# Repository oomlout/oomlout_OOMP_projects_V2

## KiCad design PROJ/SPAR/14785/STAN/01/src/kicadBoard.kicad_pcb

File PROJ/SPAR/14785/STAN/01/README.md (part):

Contents
========

* [PRPR14785 > Pro RF](#prpr14785--pro-rf)
	* [OOMP Parts](#oomp-parts)
	* [Images](#images)
	* [Tags](#tags)
  
![][im]
# PRPR14785 > Pro RF

- ID: PROJ-SPAR-14785-STAN-01
- Hex ID: PRPR14785
- Name: Pro RF
- Path: oomlout_OOMP_projects_V2/PROJ/SPAR/14785/STAN/01/
- Description: Pro RF
- Long Link: [http://oom.lt/PROJ-SPAR-14785-STAN-01](http://oom.lt/PROJ-SPAR-14785-STAN-01)
- Short Link: [http://oom.lt/PRPR14785](http://oom.lt/PRPR14785)

## OOMP Parts

|Image|OOMP ID|Designators|
| :--- | :--- | :--- |
||[CAPC-0603-X-NF100-V50](https://github.com/oomlout/oomlout_OOMP_parts_V2/tree/main/CAPC/0603/X/NF100/V50/)|[C14,C11,C4](https://github.com/oomlout/oomlout_OOMP_parts_V2/tree/main/CAPC/0603/X/NF100/V50/)|
||[CAPC-0603-X-PF22-V50](https://github.com/oomlout/oomlout_OOMP_parts_V2/tree/main/CAPC/0603/X/PF22/V50/)|[C7,C5](https://github.com/oomlout/oomlout_OOMP_parts_V2/tree/main/CAPC/0603/X/PF22/V50/)|
||[CAPC-0603-X-UF1-V50](https://github.com/oomlout/oomlout_OOMP_parts_V2/tree/main/CAPC/0603/X/UF1/V50/)|[C12,C8](https://github.com/oomlout/oomlout_OOMP_parts_V2/tree/main/CAPC/0603/X/UF1/V50/)|
||[CAPC-0603-X-UF47D-V16](https://github.com/oomlout/oomlout_OOMP_parts_V2/tree/main/CAPC/0603/X/UF47D/V16/)|[C9](https://github.com/oomlout/oomlout_OOMP_parts_V2/tree/main/CAPC/0603/X/UF47D/V16/)|
||CAPT-3216-X-UF10-V10|C13,C1|
||[HEAD-I01-X-PI01-01](https://github.com/oomlout/oomlout_OOMP_parts_V2/tree/main/HEAD/I01/X/PI01/01/)|[J4](https://github.com/oomlout/oomlout_OOMP_parts_V2/tree/main/HEAD/I01/X/PI01/01/)|
||[HEAD-I01-X-PI02-01](https://github.com/oomlout/oomlout_OOMP_parts_V2/tree/main/HEAD/I01/X/PI02/01/)|[J7,J12,J9,J8](https://github.com/oomlout/oomlout_OOMP_parts_V2/tree/main/HEAD/I01/X/PI02/01/)|
||[HEAD-I01-X-PI09-01](https://github.com/oomlout/oomlout_OOMP_parts_V2/tree/main/HEAD/I01/X/PI09/01/)|[J11,J5](https://github.com/oomlout/oomlout_OOMP_parts_V2/tree/main/HEAD/I01/X/PI09/01/)|
||[HEAD-I01-X-PI10-01](https://github.com/oomlout/oomlout_OOMP_parts_V2/tree/main/HEAD/I01/X/PI10/01/)|[J6,J3](https://github.com/oomlout/oomlout_OOMP_parts_V2/tree/main/HEAD/I01/X/PI10/01/)|
||HEAD-I01-X-UNMATCHED-01|J13|
||[HEAD-JSTSH-X-PI04-RS](https://github.com/oomlout/oomlout_OOMP_parts_V2/tree/main/HEAD/JSTSH/X/PI04/RS/)|[J2](https://github.com/oomlout/oomlout_OOMP_parts_V2/tree/main/HEAD/JSTSH/X/PI04/RS/)|
||[LEDS-0603-G-STAN-01](https://github.com/oomlout/oomlout_OOMP_parts_V2/tree/main/LEDS/0603/G/STAN/01/)|[D1](https://github.com/oomlout/oomlout_OOMP_parts_V2/tree/main/LEDS/0603/G/STAN/01/)|
||[LEDS-0603-L-STAN-01](https://github.com/oomlout/oomlout_OOMP_parts_V2/tree/main/LEDS/0603/L/STAN/01/)|[D2](https://github.com/oomlout/oomlout_OOMP_parts_V2/tree/main/LEDS/0603/L/STAN/01/)|
||[LEDS-0603-R-STAN-01](https://github.com/oomlout/oomlout_OOMP_parts_V2/tree/main/LEDS/0603/R/STAN/01/)|[LED1](https://github.com/oomlout/oomlout_OOMP_parts_V2/tree/main/LEDS/0603/R/STAN/01/)|
||[LEDS-0603-Y-STAN-01](https://github.com/oomlout/oomlout_OOMP_parts_V2/tree/main/LEDS/0603/Y/STAN/01/)|[D6,D4](https://github.com/oomlout/oomlout_OOMP_parts_V2/tree/main/LEDS/0603/Y/STAN/01/)|
||[RESE-0603-X-O102-01](https://github.com/oomlout/oomlout_OOMP_parts_V2/tree/main/RESE/0603/X/O102/01/)|[R13,R9,R3,R10,R7](https://github.com/oomlout/oomlout_OOMP_parts_V2/tree/main/RESE/0603/X/O102/01/)|
||[RESE-0603-X-O103-01](https://github.com/oomlout/oomlout_OOMP_parts_V2/tree/main/RESE/0603/X/O103/01/)|[R4,R6,R1,R2](https://github.com/oomlout/oomlout_OOMP_parts_V2/tree/main/RESE/0603/X/O103/01/)|
||[RESE-0603-X-O202-01](https://github.com/oomlout/oomlout_OOMP_parts_V2/tree/main/RESE/0603/X/O202/01/)|[R5](https://github.com/oomlout/oomlout_OOMP_parts_V2/tree/main/RESE/0603/X/O202/01/)|
||[RESE-0603-X-O220-01](https://github.com/oomlout/oomlout_OOMP_parts_V2/tree/main/RESE/0603/X/O220/01/)|[R11,R12](https://github.com/oomlout/oomlout_OOMP_parts_V2/tree/main/RESE/0603/X/O220/01/)|
||UNMATCHED-1206-X-UNMATCHED-01|F1|
||UNMATCHED-SO235-X-UNMATCHED-01|U1,U6|
||UNMATCHED-UNMATCHED-X-UNMATCHED-01|U3,Y2,S3,S1,U2|
||USBS-UNMATCHED-X-UNMATCHED-01|J1|
||||

## Images

|kicadPcb3dFront<br>|kicadPcb3dBack<br>|kicadPcb3d<br>|pcbdraw<br>|
| :---: | :---: | :---: | :---: |
|pcbdrawBack<br>||||

## Tags

|Tag Name|Tag Code|Tag Value|
| :--- | :--- | :--- |
|OOMP Type|oompType|PROJ|
|OOMP Size|oompSize|SPAR|
|OOMP Color|oompColor|14785|
|OOMP Description|oompDesc|STAN|
|OOMP Index|oompIndex|01|
|Full OOMP ID|oompID|PROJ-SPAR-14785-STAN-01|
|Hex ID (short code)|hexID|PRPR14785|
|name|name|Pro RF|
|gitRepo|gitRepo|https://github.com/sparkfun/Pro_RF|
|gitName|gitName|Pro_RF|
|eagleBoard|eagleBoard|/Hardware/Pro_RF.brd|
|eagleSchem|eagleSchem|/Hardware/Pro_RF.sch|
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
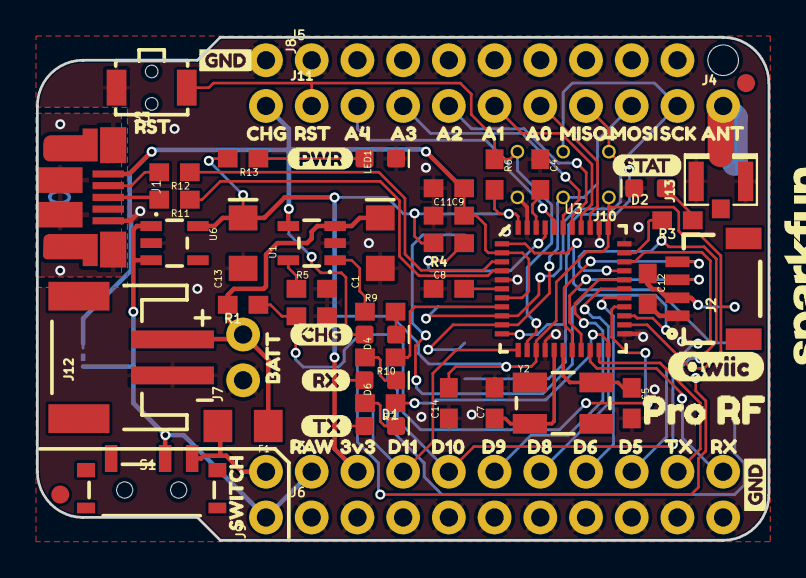
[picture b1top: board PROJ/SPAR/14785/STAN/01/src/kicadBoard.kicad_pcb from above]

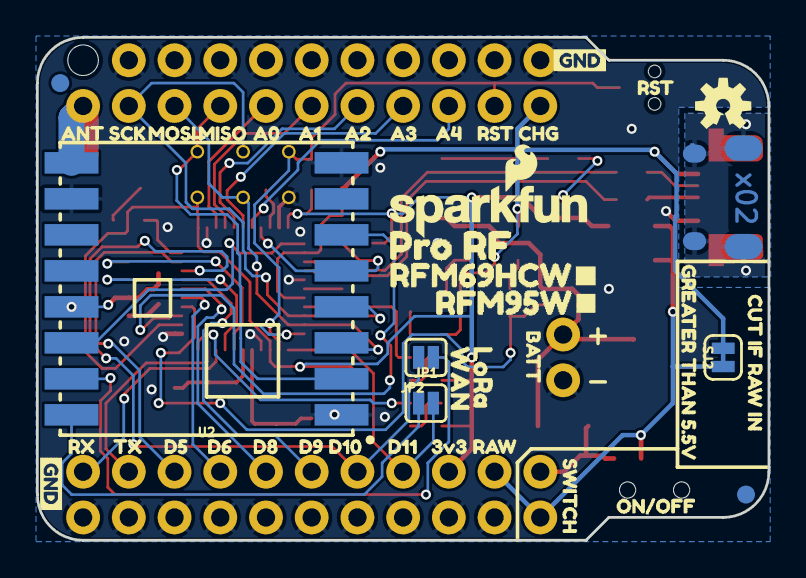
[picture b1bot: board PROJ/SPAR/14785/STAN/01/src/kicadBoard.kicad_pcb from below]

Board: 2 copper layers, 40.6 x 27.9 mm, 129 parts (42 on the bottom side), 51 nets.

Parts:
@HOLE0: (no value)
C1, C13: 10uF; EIA3216
C4, C11, C14: 0.1uF; 0603
C5, C7: 22pF; 0603
C8, C12: 1.0uF; 0603
C9: 4.7uF; 0603
D1: Green; LED-0603
D2: BLUE; LED-0603
D4, D6: Yellow; LED-0603
F1: 6V/0.5A; 1206
FD1, FD2, FD3, FD4: FIDUCIAL1X2; FIDUCIAL-1X2
FRAME2: FRAME-LEDGER; CREATIVE_COMMONS
J1: USB-MICROB-PTH-MILL
J2: 1X04_1MM_RA
J3, J6: 1X10_NO_SILK
J4: 1X01_NO_SILK
J5, J11: 1X09_NO_SILK
J7: PTH; 1X02_NO_SILK
J8: 1X02_NO_SILK
J9: External On/Off; 1X02_NO_SILK
J10: AVR_SPI_PROG_3X2TESTPOINTS; 2X3_TEST_POINTS
J12: JST; JST-2-SMD
J13: U.FL
JP1, JP2: SMT-JUMPER_2_NO_SILK
LED1: RED; LED-0603
LOGO1: REVISION
LOGO2: SFE_LOGO_NAME.1_INCH; SFE_LOGO_NAME_.1
LOGO3: SFE_LOGO_NAME_FLAME.1_INCH; SFE_LOGO_NAME_FLAME_.1
R1, R2, R4, R6: 10k; 0603
R3, R7, R9, R10, R13: 1k; 0603
R5: 2.0k; 0603
R11, R12: 22; 0603
S1: Power; SWITCH_SPST_SMD_A
S3: TACTILE_SWITCH_SMD_RIGHT_ANGLE
SJ2: USB Power; SMT-JUMPER_2_NC_TRACE_SILK
U1: MCP73831; SOT23-5
U2: 915MHz; RFM69HCW-XXXS2
U3: 32U4; QFN-44-NOPAD
U6: 3.3V; SOT23-5
U$1, U$31: PRO_RF0
U$3, U$42: A43
U$4, U$43: A34
U$5, U$44: A25
U$6, U$45: A16
U$7, U$46: A07
U$8, U$47: MISO8
U$9, U$48: MOSI9
U$10, U$49: SCK10
U$11, U$50: ANT11
U$12, U$17, U$38, U$62: GND0
U$13, U$28, U$36, U$41: RST2
U$14, U$40, U$65: CHG1
U$15, U$16: D90
U$18, U$58: D615
U$19, U$73: RX2
U$20, U$56: D817
U$21, U$68: D100
U$22, U$54: D1119
U$23, U$53: 3V320
U$24, U$52: RAW21
U$25: LORA0
U$26: SPECIAL_INSTRUCTIONS-ORDERING; ORDERING_INSTRUCTIONS
U$27, U$37: SWITCH23
U$29, U$32: BATT25
U$33: CUT_IF_RAW_IN0
U$34: GREATER_THAN_5#5V1
U$35: WAN1
U$39: ON#OFF0
U$51: OSHW-LOGO-S
U$55, U$74: D514
U$57, U$69: TX3
U$59: RFM69HCW#1
U$60: RFM95W#0
U$63: PWR-()-03
U$66: QWIIC-()-04
U$70: TX6
U$71: STAT5
U$72: RX7
Y2: 8MHz; CRYSTAL-SMD-5X3.2-4PAD

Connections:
3.3V: C12.1, C13.+, C14.2, D1.A, D6.A, J2.2, J3.2, J10.2, R4.2, R6.2, R13.2, U2.13, U3.14, U3.24, U3.34, U3.44, U6.5
A0: J11.6, U3.36
A1: J11.5, U3.37
A2: J11.4, U3.38
A3: J11.3, U3.39
A4: J11.2, U3.40
ANT: J4.1, J13.FEED, U2.9
AREF: C4.2, U3.42
CHARGE_STAT: R9.1, U1.1
D5: J3.8, U3.31
D6: J3.7, U3.27
D8: J3.6, U3.28
D9: J3.5, U3.29
D10: J3.4, JP1.2, U3.30
D11: J3.3, JP2.2, U3.12
D+: R11.1, U3.4
D-: R12.1, U3.3
GND: C1.-, C4.1, C5.2, C7.2, C8.1, C9.2, C11.1, C12.2, C13.-, C14.1, D2.C, J1.GND, J2.1, J5.1, J5.2, J5.3, J5.4, J5.5, J5.6, J5.7, J5.8, J5.9, J6.1, J6.2, J6.3, J6.4, J6.5, J6.6, J6.7, J6.8, J6.9, J6.10, J7.1, J8.1, J10.6, J12.1, J13.1, J13.2, LED1.C, R2.1, R5.2, S3.2, U1.2, U2.1, U2.8, U2.10, U3.5, U3.15, U3.23, U3.33, U3.35, U3.43, U6.2
MISO: J10.1, J11.7, U2.2, U3.11
MOSI: J10.4, J11.8, U2.3, U3.10
unnamed: D6.C, R10.2
unnamed: D1.C, R7.2
unnamed: D2.A, R3.1
unnamed: C5.1, U3.17, Y2.3
unnamed: J1.D+, R11.2
unnamed: C7.1, U3.16, Y2.1
unnamed: D4.C, R9.2
unnamed: F1.2, J9.2, S1.1
unnamed: R5.1, U1.5
unnamed: J1.D-, R12.2
unnamed: LED1.A, R13.1
RAW: J3.1, J9.1, S1.2, SJ2.1, U6.1, U6.3
RFM_INT: U2.14, U3.1
RFM_IO1: JP1.1, U2.15
RFM_IO2: JP2.1, U2.16
RFM_RST: U2.6, U3.25
RXI: J3.10, U3.20
RXLED: R10.1, U3.8
SCK: J10.3, J11.9, U2.4, U3.9
SCL: J2.4, U3.18
SDA: J2.3, U3.19
SHLD: J1.SHIELD, J1.SHIELD2, J1.SHIELD3, J1.SHIELD4, J1.SHIELD5, J1.SHIELD6, J1.SHIELD7, J1.SHIELD8, J1.SHIELD9, J1.SHIELD10
STAT: R3.2, U3.32
TXLED: R7.1, U3.22
TXO: J3.9, U3.21
UCAP: C8.2, U3.6
USB_VCC: C9.1, C11.2, D4.A, J1.VBUS, J8.2, SJ2.2, U1.4, U3.2, U3.7
VBATT: C1.+, F1.1, J7.2, J12.2, R1.2, U1.3
VBATT_LVL: R1.1, R2.2, U3.26
~CS: R4.1, U2.5, U3.41
~RST: J10.5, J11.1, R6.1, S3.1, U3.13

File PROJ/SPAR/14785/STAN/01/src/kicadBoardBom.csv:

"Id";"Designator";"Package";"Quantity";"Designation";"Supplier and ref";
1;"J1";"USB-MICROB-PTH-MILL";1;"";;;
2;"J7";"1X02_NO_SILK";1;"PTH";;;
3;"U3";"QFN-44-NOPAD";1;"32U4";;;
4;"U$28,U$13,U$36,U$41";"RST2";4;"";;;
5;"U$15,U$16";"D90";2;"";;;
6;"Y2";"CRYSTAL-SMD-5X3.2-4PAD";1;"8MHz";;;
7;"U$66";"QWIIC-()-04";1;"";;;
8;"D6,D4";"LED-0603";2;"Yellow";;;
9;"R4,R6,R1,R2";"0603";4;"10k";;;
10;"C14,C11,C4";"0603";3;"0.1uF";;;
11;"J6,J3";"1X10_NO_SILK";2;"";;;
12;"D1";"LED-0603";1;"Green";;;
13;"J4";"1X01_NO_SILK";1;"";;;
14;"R11,R12";"0603";2;"22";;;
15;"LED1";"LED-0603";1;"RED";;;
16;"U$72";"RX7";1;"";;;
17;"S3";"TACTILE_SWITCH_SMD_RIGHT_ANGLE";1;"";;;
18;"LOGO2";"SFE_LOGO_NAME_.1";1;"SFE_LOGO_NAME.1_INCH";;;
19;"R13,R9,R3,R10,R7";"0603";5;"1k";;;
20;"U$29,U$32";"BATT25";2;"";;;
21;"D2";"LED-0603";1;"BLUE";;;
22;"U$11,U$50";"ANT11";2;"";;;
23;"U$18,U$58";"D615";2;"";;;
24;"J11,J5";"1X09_NO_SILK";2;"";;;
25;"J2";"1X04_1MM_RA";1;"";;;
26;"C12,C8";"0603";2;"1.0uF";;;
27;"U$73,U$19";"RX2";2;"";;;
28;"U$68,U$21";"D100";2;"";;;
29;"U$65,U$14,U$40";"CHG1";3;"";;;
30;"U$26";"ORDERING_INSTRUCTIONS";1;"SPECIAL_INSTRUCTIONS-ORDERING";;;
31;"C7,C5";"0603";2;"22pF";;;
32;"FD4,FD3,FD1,FD2";"FIDUCIAL-1X2";4;"FIDUCIAL1X2";;;
33;"U$62,U$12,U$38,U$17";"GND0";4;"";;;
34;"J13";"U.FL";1;"U.FL";;;
35;"U$1,U$31";"PRO_RF0";2;"";;;
36;"U$6,U$45";"A16";2;"";;;
37;"U$7,U$46";"A07";2;"";;;
38;"U$27,U$37";"SWITCH23";2;"";;;
39;"U$23,U$53";"3V320";2;"";;;
40;"U$69,U$57";"TX3";2;"";;;
41;"J12";"JST-2-SMD";1;"JST";;;
42;"C9";"0603";1;"4.7uF";;;
43;"R5";"0603";1;"2.0k";;;
44;"U$4,U$43";"A34";2;"";;;
45;"J10";"2X3_TEST_POINTS";1;"AVR_SPI_PROG_3X2TESTPOINTS";;;
46;"U$70";"TX6";1;"";;;
47;"U$9,U$48";"MOSI9";2;"";;;
48;"LOGO1";"REVISION";1;"REVISION";;;
49;"U$71";"STAT5";1;"";;;
50;"J9";"1X02_NO_SILK";1;"External On/Off";;;
51;"F1";"1206";1;"6V/0.5A";;;
52;"@HOLE0";"";1;"";;;
53;"J8";"1X02_NO_SILK";1;"";;;
54;"C13,C1";"EIA3216";2;"10uF";;;
55;"S1";"SWITCH_SPST_SMD_A";1;"Power";;;
56;"U$5,U$44";"A25";2;"";;;
57;"U$8,U$47";"MISO8";2;"";;;
58;"FRAME2";"CREATIVE_COMMONS";1;"FRAME-LEDGER";;;
59;"U$63";"PWR-()-03";1;"";;;
60;"U1";"SOT23-5";1;"MCP73831";;;
61;"U$24,U$52";"RAW21";2;"";;;
62;"U$10,U$49";"SCK10";2;"";;;
63;"U6";"SOT23-5";1;"3.3V";;;
64;"U$3,U$42";"A43";2;"";;;
65;"U$22,U$54";"D1119";2;"";;;
66;"U$55,U$74";"D514";2;"";;;
67;"U$20,U$56";"D817";2;"";;;
68;"U$39";"ON#OFF0";1;"";;;
69;"U$51";"OSHW-LOGO-S";1;"";;;
70;"U$60";"RFM95W#0";1;"";;;
71;"U$59";"RFM69HCW#1";1;"";;;
72;"U$25";"LORA0";1;"";;;
73;"SJ2";"SMT-JUMPER_2_NC_TRACE_SILK";1;"USB Power";;;
74;"U$33";"CUT_IF_RAW_IN0";1;"";;;
75;"U$35";"WAN1";1;"";;;
76;"JP2,JP1";"SMT-JUMPER_2_NO_SILK";2;"";;;
77;"U2";"RFM69HCW-XXXS2";1;"915MHz";;;
78;"U$34";"GREATER_THAN_5#5V1";1;"";;;
79;"LOGO3";"SFE_LOGO_NAME_FLAME_.1";1;"SFE_LOGO_NAME_FLAME.1_INCH";;;

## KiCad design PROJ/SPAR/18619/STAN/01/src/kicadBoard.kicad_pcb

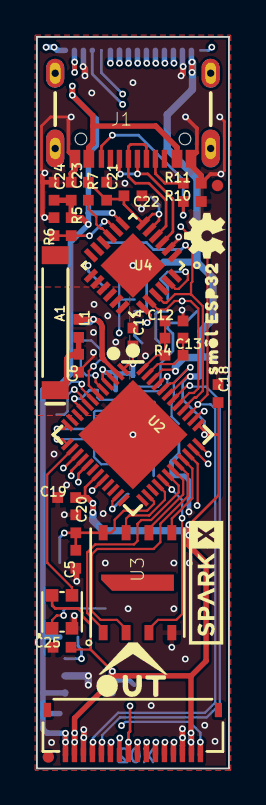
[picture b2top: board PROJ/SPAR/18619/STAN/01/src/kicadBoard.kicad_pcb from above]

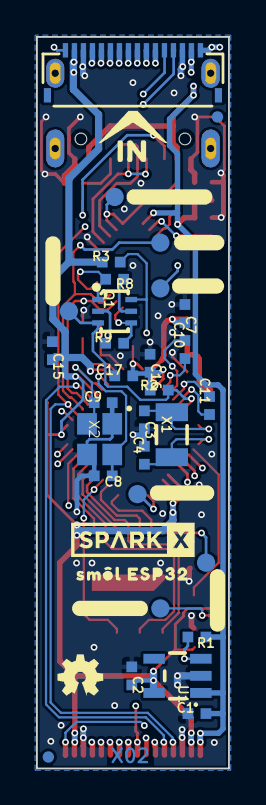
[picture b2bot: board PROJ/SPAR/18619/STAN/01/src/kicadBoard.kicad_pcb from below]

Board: 4 copper layers, 10.7 x 40.6 mm, 80 parts (43 on the bottom side), 50 nets.

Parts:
!BOOT!0: TEST-POINT3X4; PAD.03X.04
!RESET!0: TEST-POINT3X4; PAD.03X.04
A1: ANTENNA2.4GHZ-8.0X1.0MM; ANT-2.4GHZ-8.0X1.0MM
C1, C2: 2.2uF; 0402-TIGHT
C3, C4: 15pF; 0402-TIGHT
C5, C15, C16, C18, C19, C22, C23, C25: 0.1uF; 0402-TIGHT
C6, C7: DNP; 0402-TIGHT_NO_CREAM
C8, C9: 12pF; 0402-TIGHT
C10, C11: 270pF; 0402-TIGHT
C12: 10nF; 0402-TIGHT
C13: 3.0nF; 0402-TIGHT
C14: 100pF; 0402-TIGHT
C17: 10uF; 0402-TIGHT
C20: 1.0uF; 0402-TIGHT
C21, C24: 4.7uF; 0402-TIGHT
D1: WS2812_2020; WS2812-2020
FD1, FD2, FD3, FD4: FIDUCIALUFIDUCIAL; FIDUCIAL-MICRO
FLASH_VDD0: TEST-POINT3X4; PAD.03X.04
FRAME1: FRAME-LEDGER; CREATIVE_COMMONS
IN0: FPC_16_0.5MM
J1: USB-C-16P_4LAYER-PADS
L1: 0; 0402-TIGHT
LED_DO0: TEST-POINT3X4; PAD.03X.04
LOGO1: SPECIAL_INSTRUCTIONS-ORDERING; ORDERING_INSTRUCTIONS
LOGO2, LOGO3: OSHW-LOGOMINI; OSHW-LOGO-MINI
LOGO4: SPECIAL_INSTRUCTIONS-PRODUCTION; PRODUCTION_INSTRUCTIONS
OUT0: FPC_16_0.5MM
Q1: MBT3904DW1T1; SC70-6
R1: 100k; 0402-TIGHT
R2, R3, R8, R9: 10k; 0402-TIGHT
R4: 20k; 0402-TIGHT
R5: 22k; 0402-TIGHT
R6: 33k; 0402-TIGHT
R7: 2.2k; 0402-TIGHT
R10, R11: 5.1k; 0402-TIGHT
RXD0: TEST-POINT3X4; PAD.03X.04
TXD0: TEST-POINT3X4; PAD.03X.04
U1: MIC5219 3.3V; SOT23-5
U2: ESP32; QFN48-0.4MM
U3: W25QXX128MBIT-6X5-SKINNY_CENTER; WSON-8-6X5-SKINNY_CENTERPAD
U4: CP2102N; QFN24
U$1, U$4: SPARKX-LOGO3; SPARKX-SMALL
U$5, U$17: SM�L_ESP320
U$6: #TXD#0
U$7: ##BOOT##0
U$8: ##RESET##0
U$9: #USB_3V3#0
U$10: #FVDD#0
U$11: #LED_DO#0
U$12: IN0
U$13: OUT0
U$14, U$15: SMOL_LOGOSMALL; SMOL_SMALL
U$16: #RXD#0
USB_3V3: TEST-POINT3X4; PAD.03X.04
X1: 32.768kHz; CRYSTAL-SMD-3.2X1.5MM
X2: 40MHz; CRYSTAL-SMD-2X2.5MM

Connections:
0-~BOOT: !BOOT!0.1, Q1.6, R3.1, U2.23
1: C11.1, U2.7
3: C10.2, U2.5
3.3V: C2.1, C14.1, C15.1, C16.1, C17.1, C18.1, C19.1, C25.1, D1.VCC, IN0.2, IN0.15, OUT0.2, OUT0.15, R2.2, R3.2, U1.5, U2.1, U2.3, U2.4, U2.19, U2.37, U2.43, U2.46
6: C10.1, U2.6
32-RTC: C3.2, U2.12, X1.P$1
33-RTC: C4.2, U2.13, X1.P$2
CAP_10N1: C12.2, C13.1, R4.2, U2.48
CIPO: IN0.6, OUT0.6, U2.38
COPI: IN0.5, OUT0.5, U2.36
CS0: IN0.7, OUT0.7, U2.34
CS1: IN0.8, OUT0.8, U2.17
CS2: IN0.9, OUT0.9, U2.20
D+: J1.A6, J1.B6, U4.3
D-: J1.A7, J1.B7, U4.4
DTR: Q1.1, R8.1, U4.23
FLASH_SCK: U2.31, U3.6
FLASH_SCS: U2.30, U3.1
FLASH_SDI: U2.33, U3.5
FLASH_SDO: U2.32, U3.2
FLASH_SHD: U2.28, U3.7
FLASH_SWP: U2.29, U3.3
FLASH_VDD: C5.1, C20.1, FLASH_VDD0.1, U2.26, U3.8
GND: C1.2, C2.2, C3.1, C4.1, C5.2, C6.2, C7.2, C8.1, C9.1, C12.1, C14.2, C15.2, C16.2, C17.2, C18.2, C19.2, C20.2, C21.2, C22.2, C23.2, C24.2, C25.2, D1.GND, IN0.3, IN0.14, J1.GND, J1.GND2, OUT0.3, OUT0.14, R6.1, R10.1, R11.1, U1.2, U2.EP, U3.4, U4.2, U4.PAD, X2.P2, X2.P4
GPIO0: IN0.10, OUT0.10, U2.16
GPIO1: IN0.11, OUT0.11, U2.15
LED: D1.DI, U2.14
unnamed: J1.A5, R11.2
unnamed: J1.B5, R10.2
unnamed: C11.2, U2.8
unnamed: D1.DO, LED_DO0.1
unnamed: Q1.5, R8.2
unnamed: Q1.2, R9.2
unnamed: C8.2, U2.45, X2.P1
unnamed: C9.2, U2.44, X2.P3
unnamed: C13.2, R4.1, U2.47
unnamed: R5.1, R6.2, U4.8
unnamed: R7.1, U4.9
unnamed: A1.FEED, C6.1, L1.1
unnamed: C7.1, L1.2, U2.2
PROC_PWR_EN: IN0.1, OUT0.1, R1.1, U1.3
RTS: Q1.4, R9.1, U4.19
SCL: IN0.13, OUT0.13, U2.39
SCLK: IN0.4, OUT0.4, U2.35
SDA: IN0.12, OUT0.12, U2.42
U0RXD: RXD0.1, U2.40, U4.21
U0TXD: TXD0.1, U2.41, U4.20
USB_3V3: C21.1, C22.1, R7.2, U4.5, U4.6, USB_3V3.1
V_USB: C1.1, C23.1, C24.1, IN0.16, J1.VBUS1, J1.VBUS2, OUT0.16, R1.2, R5.2, U1.1, U4.7
~RESET: !RESET!0.1, Q1.3, R2.1, U2.9

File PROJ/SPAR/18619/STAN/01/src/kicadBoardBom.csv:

"Id";"Designator";"Package";"Quantity";"Designation";"Supplier and ref";
1;"C25,C22,C19,C18,C5,C23,C15,C16";"0402-TIGHT";8;"0.1uF";;;
2;"U3";"WSON-8-6X5-SKINNY_CENTERPAD";1;"W25QXX128MBIT-6X5-SKINNY_CENTER";;;
3;"A1";"ANT-2.4GHZ-8.0X1.0MM";1;"ANTENNA2.4GHZ-8.0X1.0MM";;;
4;"C14";"0402-TIGHT";1;"100pF";;;
5;"C21,C24";"0402-TIGHT";2;"4.7uF";;;
6;"J1";"USB-C-16P_4LAYER-PADS";1;"";;;
7;"R7";"0402-TIGHT";1;"2.2k";;;
8;"R10,R11";"0402-TIGHT";2;"5.1k";;;
9;"C20";"0402-TIGHT";1;"1.0uF";;;
10;"LOGO2,LOGO3";"OSHW-LOGO-MINI";2;"OSHW-LOGOMINI";;;
11;"LOGO1";"ORDERING_INSTRUCTIONS";1;"SPECIAL_INSTRUCTIONS-ORDERING";;;
12;"FD3,FD1,FD2,FD4";"FIDUCIAL-MICRO";4;"FIDUCIALUFIDUCIAL";;;
13;"U4";"QFN24";1;"CP2102N";;;
14;"R4";"0402-TIGHT";1;"20k";;;
15;"FRAME1";"CREATIVE_COMMONS";1;"FRAME-LEDGER";;;
16;"U$5,U$17";"SM�L_ESP320";2;"";;;
17;"U$13";"OUT0";1;"";;;
18;"C12";"0402-TIGHT";1;"10nF";;;
19;"U$14,U$15";"SMOL_SMALL";2;"SMOL_LOGOSMALL";;;
20;"OUT0,IN0";"FPC_16_0.5MM";2;"";;;
21;"R5";"0402-TIGHT";1;"22k";;;
22;"C13";"0402-TIGHT";1;"3.0nF";;;
23;"LOGO4";"PRODUCTION_INSTRUCTIONS";1;"SPECIAL_INSTRUCTIONS-PRODUCTION";;;
24;"R6";"0402-TIGHT";1;"33k";;;
25;"L1";"0402-TIGHT";1;"0";;;
26;"D1";"WS2812-2020";1;"WS2812_2020";;;
27;"U2";"QFN48-0.4MM";1;"ESP32";;;
28;"C6,C7";"0402-TIGHT_NO_CREAM";2;"DNP";;;
29;"U$1,U$4";"SPARKX-SMALL";2;"SPARKX-LOGO3";;;
30;"R3,R2,R9,R8";"0402-TIGHT";4;"10k";;;
31;"X1";"CRYSTAL-SMD-3.2X1.5MM";1;"32.768kHz";;;
32;"TXD0,FLASH_VDD0,!BOOT!0,USB_3V3,LED_DO0,!RESET!0,RXD0";"PAD.03X.04";7;"TEST-POINT3X4";;;
33;"U$10";"#FVDD#0";1;"";;;
34;"U$16";"#RXD#0";1;"";;;
35;"R1";"0402-TIGHT";1;"100k";;;
36;"C8,C9";"0402-TIGHT";2;"12pF";;;
37;"C1,C2";"0402-TIGHT";2;"2.2uF";;;
38;"U1";"SOT23-5";1;"MIC5219 3.3V";;;
39;"U$6";"#TXD#0";1;"";;;
40;"C11,C10";"0402-TIGHT";2;"270pF";;;
41;"U$9";"#USB_3V3#0";1;"";;;
42;"C3,C4";"0402-TIGHT";2;"15pF";;;
43;"U$11";"#LED_DO#0";1;"";;;
44;"U$7";"##BOOT##0";1;"";;;
45;"C17";"0402-TIGHT";1;"10uF";;;
46;"X2";"CRYSTAL-SMD-2X2.5MM";1;"40MHz";;;
47;"U$12";"IN0";1;"";;;
48;"U$8";"##RESET##0";1;"";;;
49;"Q1";"SC70-6";1;"MBT3904DW1T1";;;

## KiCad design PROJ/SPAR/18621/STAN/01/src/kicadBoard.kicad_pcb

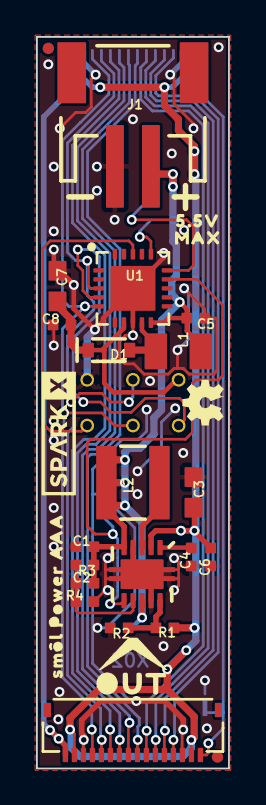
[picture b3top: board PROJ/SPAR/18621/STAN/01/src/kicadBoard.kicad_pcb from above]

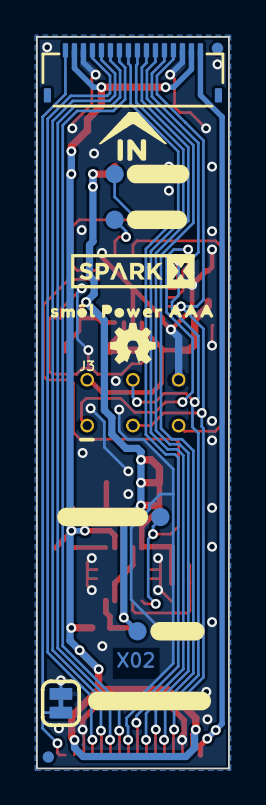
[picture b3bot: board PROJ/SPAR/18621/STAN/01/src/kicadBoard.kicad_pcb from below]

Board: 2 copper layers, 10.7 x 40.6 mm, 49 parts (19 on the bottom side), 26 nets.

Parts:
C1: 10uF; 0402-TIGHT
C2, C4, C6, C8: 0.1uF; 0402-TIGHT
C3, C7: 22uF; 0603
C5: 4.7uF; 0402-TIGHT
D1: 1A/23V/620mV; SOD-323
FD1, FD2, FD3, FD4: FIDUCIALUFIDUCIAL; FIDUCIAL-MICRO
FRAME1: FRAME-LEDGER; CREATIVE_COMMONS
IN0: FPC_16_0.5MM
J1: JST-2-SMD
J3: AVR_SPI_PROG_3X2TESTPOINTS; 2X3_TEST_POINTS
L1: 15uH; INDUCTOR_LQH32
L2: 4.7μH; INDUCTOR_4X4MM
LOGO1: SPECIAL_INSTRUCTIONS-ORDERING; ORDERING_INSTRUCTIONS
LOGO2, LOGO3: OSHW-LOGOMINI; OSHW-LOGO-MINI
OUT0: FPC_16_0.5MM
PROC_PWR_EN0: JUMPER-SMT_2_NC_TRACE_SILK; SMT-JUMPER_2_NC_TRACE_SILK
R1: 1M; 0402-TIGHT
R2: 180k; 0402-TIGHT
R3: 453k; 0402-TIGHT
R4: 150K; 0402-TIGHT
RXD0: TEST-POINT3X4; PAD.03X.04
TXD0: TEST-POINT3X4; PAD.03X.04
U1: ATTINY43_QFN20; QFN20_20M1
U2: TPS61200; QFN-10_PAD
U$1, U$20: SPARKX-LOGO3; SPARKX-SMALL
U$2, U$8: SM�L_POWER_AAA0
U$3: OUT0
U$4: #TXD#0
U$5: #VIN#0
U$6: #3V3_EN#0
U$7: #PROC_PWR#0
U$9: #RXD#0
U$10: 5#5V0
U$11: MAX0
U$12: IN0
U$13, U$14: SMOL_LOGOSMALL; SMOL_SMALL
UNK3V3_EN0: TEST-POINT3X4; PAD.03X.04
VIN0: TEST-POINT3X4; PAD.03X.04

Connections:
3.3V: C3.1, C6.1, IN0.2, IN0.15, OUT0.2, OUT0.15, R1.2, U2.2
3V3_EN: U1.14, U2.6, UNK3V3_EN0.1
AT_CIPO: J3.1, U1.4
AT_VCC: C7.1, C8.1, D1.C, J3.2, U1.7
CIPO: IN0.6, OUT0.6
COPI: IN0.5, OUT0.5
CS0: IN0.7, OUT0.7
CS1: IN0.8, OUT0.8
CS2: IN0.9, OUT0.9
FB: R1.1, R2.2, U2.10
GND: C1.2, C3.2, C4.2, C5.2, C6.2, C7.2, C8.2, IN0.3, IN0.14, J1.1, J3.6, OUT0.3, OUT0.14, PROC_PWR_EN0.2, R2.1, R4.1, U1.8, U1.PAD, U2.4, U2.9, U2.11, U2.12, U2.13, U2.14, U2.15
GPIO0: IN0.10, OUT0.10
GPIO1: IN0.11, OUT0.11
unnamed: L2.P$1, U2.3
unnamed: D1.A, L1.P$1, U1.9
unnamed: C4.1, U2.1
PROC_PWR_EN: IN0.1, OUT0.1, PROC_PWR_EN0.1
RXD: RXD0.1, U1.16
SCL: IN0.13, J3.3, OUT0.13, U1.5
SCLK: IN0.4, OUT0.4
SDA: IN0.12, J3.4, OUT0.12, U1.3
TXD: TXD0.1, U1.15
UVLO: C2.2, R3.1, R4.2, U2.7
VIN: C1.1, C2.1, C5.1, J1.2, L1.P$2, L2.P$2, R3.2, U1.10, U2.5, U2.8, VIN0.1
V_USB: IN0.16, OUT0.16
~RESET: J3.5, U1.18

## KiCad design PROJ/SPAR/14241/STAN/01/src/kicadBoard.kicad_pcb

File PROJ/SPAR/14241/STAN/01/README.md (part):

Contents
========

* [PRPR14241 > Qwiic Air Quality Combo Board CCS811 BME280](#prpr14241--qwiic-air-quality-combo-board-ccs811-bme280)
	* [OOMP Parts](#oomp-parts)
	* [Images](#images)
	* [Tags](#tags)
  
![][im]
# PRPR14241 > Qwiic Air Quality Combo Board CCS811 BME280

- ID: PROJ-SPAR-14241-STAN-01
- Hex ID: PRPR14241
- Name: Qwiic Air Quality Combo Board CCS811 BME280
- Path: oomlout_OOMP_projects_V2/PROJ/SPAR/14241/STAN/01/
- Description: Qwiic Air Quality Combo Board CCS811 BME280
- Long Link: [http://oom.lt/PROJ-SPAR-14241-STAN-01](http://oom.lt/PROJ-SPAR-14241-STAN-01)
- Short Link: [http://oom.lt/PRPR14241](http://oom.lt/PRPR14241)

## OOMP Parts

|Image|OOMP ID|Designators|
| :--- | :--- | :--- |
||[CAPC-0603-X-NF100-V50](https://github.com/oomlout/oomlout_OOMP_parts_V2/tree/main/CAPC/0603/X/NF100/V50/)|[C1](https://github.com/oomlout/oomlout_OOMP_parts_V2/tree/main/CAPC/0603/X/NF100/V50/)|
||[CAPC-0603-X-UF1-V50](https://github.com/oomlout/oomlout_OOMP_parts_V2/tree/main/CAPC/0603/X/UF1/V50/)|[C2](https://github.com/oomlout/oomlout_OOMP_parts_V2/tree/main/CAPC/0603/X/UF1/V50/)|
||[HEAD-I01-X-PI03-01](https://github.com/oomlout/oomlout_OOMP_parts_V2/tree/main/HEAD/I01/X/PI03/01/)|[J2](https://github.com/oomlout/oomlout_OOMP_parts_V2/tree/main/HEAD/I01/X/PI03/01/)|
||[HEAD-I01-X-PI04-01](https://github.com/oomlout/oomlout_OOMP_parts_V2/tree/main/HEAD/I01/X/PI04/01/)|[J4](https://github.com/oomlout/oomlout_OOMP_parts_V2/tree/main/HEAD/I01/X/PI04/01/)|
||[HEAD-JSTSH-X-PI04-RS](https://github.com/oomlout/oomlout_OOMP_parts_V2/tree/main/HEAD/JSTSH/X/PI04/RS/)|[J3,J1](https://github.com/oomlout/oomlout_OOMP_parts_V2/tree/main/HEAD/JSTSH/X/PI04/RS/)|
||[RESE-0603-X-O104-01](https://github.com/oomlout/oomlout_OOMP_parts_V2/tree/main/RESE/0603/X/O104/01/)|[R6,R3,R4](https://github.com/oomlout/oomlout_OOMP_parts_V2/tree/main/RESE/0603/X/O104/01/)|
||RESE-0603-X-O472-01|R13,R2,R14|
||UNMATCHED-UNMATCHED-X-UNMATCHED-01|U2,U3|
||||

## Images

|kicadPcb3dFront<br>|kicadPcb3dBack<br>|kicadPcb3d<br>|pcbdraw<br>|
| :---: | :---: | :---: | :---: |
|pcbdrawBack<br>||||

## Tags

|Tag Name|Tag Code|Tag Value|
| :--- | :--- | :--- |
|OOMP Type|oompType|PROJ|
|OOMP Size|oompSize|SPAR|
|OOMP Color|oompColor|14241|
|OOMP Description|oompDesc|STAN|
|OOMP Index|oompIndex|01|
|Full OOMP ID|oompID|PROJ-SPAR-14241-STAN-01|
|Hex ID (short code)|hexID|PRPR14241|
|name|name|Qwiic Air Quality Combo Board CCS811 BME280|
|gitRepo|gitRepo|https://github.com/sparkfun/Qwiic_Air_Quality_Combo_Board-CCS811-BME280|
|gitName|gitName|Qwiic_Air_Quality_Combo_Board-CCS811-BME280|
|eagleBoard|eagleBoard|/Hardware/Qwiic_Air_Quality_Combo_Board-CCS811-BME280.brd|
|eagleSchem|eagleSchem|/Hardware/Qwiic_Air_Quality_Combo_Board-CCS811-BME280.sch|
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
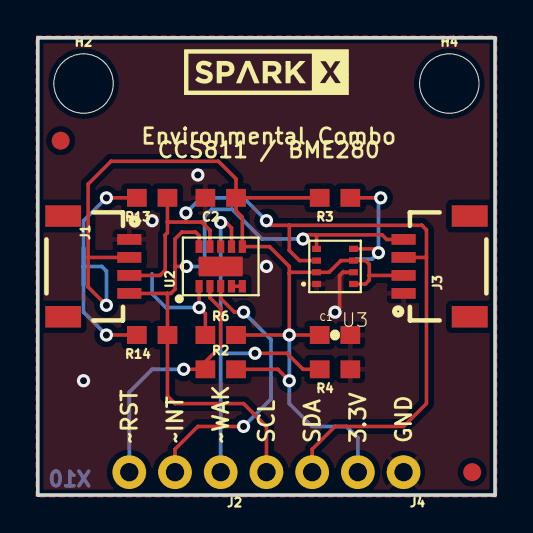
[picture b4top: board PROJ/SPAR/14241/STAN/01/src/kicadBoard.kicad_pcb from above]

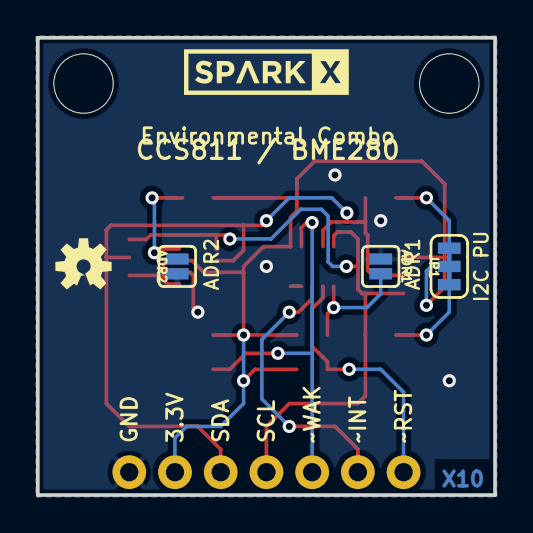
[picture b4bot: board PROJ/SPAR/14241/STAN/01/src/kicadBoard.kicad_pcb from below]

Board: 2 copper layers, 25.4 x 25.4 mm, 25 parts (5 on the bottom side), 12 nets.

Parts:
ADR1, ADR2: SMT-JUMPER_2_NO_SILK
C1: 0.1uF; 0603-CAP
C2: 1.0uF; 0603
FD1, FD2: FIDUCIAL1X2; FIDUCIAL-1X2
FRAME1: FRAME-LETTER; CREATIVE_COMMONS
H2, H4: STAND-OFF
J1, J3: JST; 1X04_1MM_RA
J2: CCS811 Options; 1X03_NO_SILK
J4: PTH; 1X04_NO_SILK
JP1: SMT-JUMPER_3_2-NC_TRACE_SILK
LOGO4: OSHW-LOGOS; OSHW-LOGO-S
R2, R13, R14: 4.7k; 0603
R3, R4, R6: 100k; 0603
U2: CCS811; LGA10
U3: BME280_LGA
U$1, U$2: SPARKX-LOGO4; SPARKX-MEDIUM

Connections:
3.3V: C1.1, C2.1, J1.2, J3.2, J4.2, JP1.2, R2.2, R3.2, R6.2, U2.6, U3.2, U3.6, U3.8
CCS811_ADDR: ADR1.2, R6.1, U2.1
GND: ADR1.1, ADR2.1, C1.2, C2.2, J1.1, J3.1, J4.1, R4.1, U2.EP, U3.1, U3.7
unnamed: JP1.3, R13.2
unnamed: JP1.1, R14.2
NTC_SENSE: U2.4, U2.5
SCL: J1.4, J3.4, J4.4, R14.1, U2.10, U3.4
SDA: J1.3, J3.3, J4.3, R13.1, U2.9, U3.3
SDO/ADR: ADR2.2, R3.1, U3.5
~INT: J2.2, U2.3
~RST: J2.3, R2.1, U2.2
~WAKE: J2.1, R4.2, U2.7

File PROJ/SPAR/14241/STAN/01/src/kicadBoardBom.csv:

"Id";"Designator";"Package";"Quantity";"Designation";"Supplier and ref";
1;"J3,J1";"1X04_1MM_RA";2;"JST";;;
2;"R13,R2,R14";"0603";3;"4.7k";;;
3;"FRAME1";"CREATIVE_COMMONS";1;"FRAME-LETTER";;;
4;"C1";"0603-CAP";1;"0.1uF";;;
5;"H4,H2";"STAND-OFF";2;"STAND-OFF";;;
6;"U2";"LGA10";1;"CCS811";;;
7;"J2";"1X03_NO_SILK";1;"CCS811 Options";;;
8;"U$1,U$2";"SPARKX-MEDIUM";2;"SPARKX-LOGO4";;;
9;"R6,R3,R4";"0603";3;"100k";;;
10;"J4";"1X04_NO_SILK";1;"PTH";;;
11;"U3";"BME280_LGA";1;"";;;
12;"FD1,FD2";"FIDUCIAL-1X2";2;"FIDUCIAL1X2";;;
13;"C2";"0603";1;"1.0uF";;;
14;"LOGO4";"OSHW-LOGO-S";1;"OSHW-LOGOS";;;
15;"JP1";"SMT-JUMPER_3_2-NC_TRACE_SILK";1;"";;;
16;"ADR1,ADR2";"SMT-JUMPER_2_NO_SILK";2;"";;;

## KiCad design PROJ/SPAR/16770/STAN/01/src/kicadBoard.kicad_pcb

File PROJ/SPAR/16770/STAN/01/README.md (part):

Contents
========

* [PRPR16770 > Qwiic PT100 ADS122C04](#prpr16770--qwiic-pt100-ads122c04)
	* [OOMP Parts](#oomp-parts)
	* [Images](#images)
	* [Tags](#tags)
  
![][im]
# PRPR16770 > Qwiic PT100 ADS122C04

- ID: PROJ-SPAR-16770-STAN-01
- Hex ID: PRPR16770
- Name: Qwiic PT100 ADS122C04
- Path: oomlout_OOMP_projects_V2/PROJ/SPAR/16770/STAN/01/
- Description: Qwiic PT100 ADS122C04
- Long Link: [http://oom.lt/PROJ-SPAR-16770-STAN-01](http://oom.lt/PROJ-SPAR-16770-STAN-01)
- Short Link: [http://oom.lt/PRPR16770](http://oom.lt/PRPR16770)

## OOMP Parts

|Image|OOMP ID|Designators|
| :--- | :--- | :--- |
||[CAPC-0603-X-NF10-V50](https://github.com/oomlout/oomlout_OOMP_parts_V2/tree/main/CAPC/0603/X/NF10/V50/)|[C5,C3](https://github.com/oomlout/oomlout_OOMP_parts_V2/tree/main/CAPC/0603/X/NF10/V50/)|
||[CAPC-0603-X-NF100-V50](https://github.com/oomlout/oomlout_OOMP_parts_V2/tree/main/CAPC/0603/X/NF100/V50/)|[C1,C2,C4](https://github.com/oomlout/oomlout_OOMP_parts_V2/tree/main/CAPC/0603/X/NF100/V50/)|
||CAPC-0603-X-NF47-01|C6|
||[CAPC-0603-X-UF1-V50](https://github.com/oomlout/oomlout_OOMP_parts_V2/tree/main/CAPC/0603/X/UF1/V50/)|[C7](https://github.com/oomlout/oomlout_OOMP_parts_V2/tree/main/CAPC/0603/X/UF1/V50/)|
||FERB-0603-X-UNMATCHED-01|FB1|
||[HEAD-I01-X-PI01-01](https://github.com/oomlout/oomlout_OOMP_parts_V2/tree/main/HEAD/I01/X/PI01/01/)|[J5,J6](https://github.com/oomlout/oomlout_OOMP_parts_V2/tree/main/HEAD/I01/X/PI01/01/)|
||[HEAD-I01-X-PI04-01](https://github.com/oomlout/oomlout_OOMP_parts_V2/tree/main/HEAD/I01/X/PI04/01/)|[J3](https://github.com/oomlout/oomlout_OOMP_parts_V2/tree/main/HEAD/I01/X/PI04/01/)|
||[HEAD-JSTSH-X-PI04-RS](https://github.com/oomlout/oomlout_OOMP_parts_V2/tree/main/HEAD/JSTSH/X/PI04/RS/)|[J2,J4](https://github.com/oomlout/oomlout_OOMP_parts_V2/tree/main/HEAD/JSTSH/X/PI04/RS/)|
||HEAD-UNMATCHED-X-UNMATCHED-01|J1|
||[LEDS-0603-R-STAN-01](https://github.com/oomlout/oomlout_OOMP_parts_V2/tree/main/LEDS/0603/R/STAN/01/)|[D1](https://github.com/oomlout/oomlout_OOMP_parts_V2/tree/main/LEDS/0603/R/STAN/01/)|
||[RESE-0603-X-O102-01](https://github.com/oomlout/oomlout_OOMP_parts_V2/tree/main/RESE/0603/X/O102/01/)|[R1](https://github.com/oomlout/oomlout_OOMP_parts_V2/tree/main/RESE/0603/X/O102/01/)|
||[RESE-0603-X-O103-01](https://github.com/oomlout/oomlout_OOMP_parts_V2/tree/main/RESE/0603/X/O103/01/)|[R5,R4](https://github.com/oomlout/oomlout_OOMP_parts_V2/tree/main/RESE/0603/X/O103/01/)|
||[RESE-0603-X-O222-01](https://github.com/oomlout/oomlout_OOMP_parts_V2/tree/main/RESE/0603/X/O222/01/)|[R3,R7,R2,R6](https://github.com/oomlout/oomlout_OOMP_parts_V2/tree/main/RESE/0603/X/O222/01/)|
||RESE-0603-X-O392-01|R10,R8|
||RESE-0603-X-UNMATCHED-01|R9|
||UNMATCHED-UNMATCHED-X-UNMATCHED-01|IC1|
||||

## Images

|kicadPcb3dFront<br>|kicadPcb3dBack<br>|kicadPcb3d<br>|pcbdraw<br>|
| :---: | :---: | :---: | :---: |
|pcbdrawBack<br>||||

## Tags

|Tag Name|Tag Code|Tag Value|
| :--- | :--- | :--- |
|OOMP Type|oompType|PROJ|
|OOMP Size|oompSize|SPAR|
|OOMP Color|oompColor|16770|
|OOMP Description|oompDesc|STAN|
|OOMP Index|oompIndex|01|
|Full OOMP ID|oompID|PROJ-SPAR-16770-STAN-01|
|Hex ID (short code)|hexID|PRPR16770|
|name|name|Qwiic PT100 ADS122C04|
|gitRepo|gitRepo|https://github.com/sparkfun/Qwiic_PT100_ADS122C04|
|gitName|gitName|Qwiic_PT100_ADS122C04|
|eagleBoard|eagleBoard|/Hardware/Qwiic_PT100.brd|
|eagleSchem|eagleSchem|/Hardware/Qwiic_PT100.sch|
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
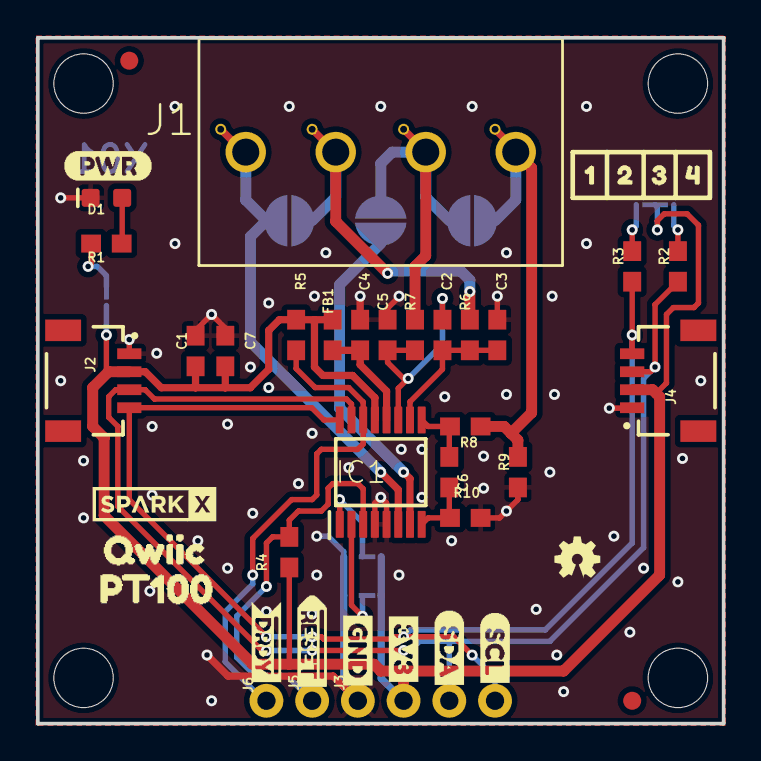
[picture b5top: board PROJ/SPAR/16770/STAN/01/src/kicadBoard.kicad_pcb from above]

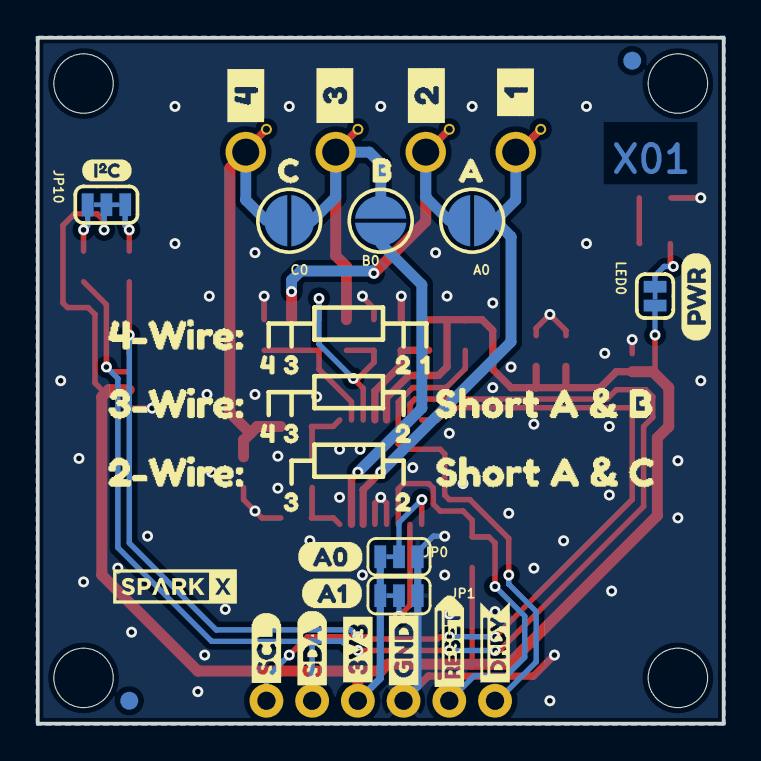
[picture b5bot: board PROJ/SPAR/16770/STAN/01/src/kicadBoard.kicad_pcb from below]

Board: 2 copper layers, 38.1 x 38.1 mm, 93 parts (41 on the bottom side), 22 nets.

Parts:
A0: JUMPER-SMT_2_NO_SILK_ROUND; SMT-JUMPER_2_NO_SILK_ROUND
B0: JUMPER-SMT_2_NO_SILK_ROUND; SMT-JUMPER_2_NO_SILK_ROUND
C0: JUMPER-SMT_2_NO_SILK_ROUND; SMT-JUMPER_2_NO_SILK_ROUND
C1, C2, C4: 0.1uF; 0603
C3, C5: 10nF; 0603
C6: 47nF; 0603
C7: 1.0uF; 0603
D1: RED; LED-0603
FB1: 30Ω/1.8A; 0603
FD1, FD2: FIDUCIAL1X2; FIDUCIAL-1X2
FRAME1: FRAME-LETTER; CREATIVE_COMMONS
H1, H2: STAND-OFF
IC1: ADS122C04IPWR; SOP65P640X120-16N
J1: LATCHTERMINAL-5MM-4
J2, J4: QWIIC_RIGHT_ANGLE; JST04_1MM_RA
J3: PTH; 1X04_NO_SILK
J5, J6: 1X01_NO_SILK
JP0, JP1: JUMPER-SMT_3_1-NC_TRACE_SILK; SMT-JUMPER_3_1-NC_TRACE_SILK
JP2, JP6: FIDUCIAL1X2; FIDUCIAL-1X2
JP3, JP4: STAND-OFF
JP10: JUMPER-SMT_3_2-NC_TRACE_SILK; SMT-JUMPER_3_2-NC_TRACE_SILK
LED0: JUMPER-SMT_2_NC_TRACE_SILK; SMT-JUMPER_2_NC_TRACE_SILK
LOGO1: OSHW-LOGOMINI; OSHW-LOGO-MINI
R1: 1k; 0603
R2, R3, R6, R7: 2.2k; 0603
R4, R5: 10k; 0603
R8, R10: 3.9k; 0603
R9: 1620; 0603
TP1, TP2, TP3, TP4: TEST-POINTTP_15TH_THRU; TP_15TH
U$1, U$2: SPARKX-LOGO3; SPARKX-SMALL
U$3, U$26: 3V33
U$4: _1_0
U$5: A11
U$6: _2_0
U$7, U$25: GND4
U$8: PT1000
U$9: SCL6
U$10: SDA5
U$11: A00
U$12: _3_0
U$13: _4_0
U$14, U$15: #DRDY0
U$16, U$17: #RESET0
U$18: A0
U$19: B0
U$20: I_SUPER2_C-()-03
U$21, U$30, U$44: 40
U$22: C0
U$23: SCL0
U$24: SDA1
U$27, U$34, U$38, U$47: 31
U$28, U$33, U$37, U$46: 20
U$29, U$35: 15
U$31: 2#WIRE#0
U$32: QWIIC1
U$36: 3#WIRE#0
U$39, U$40: PWR0
U$41: 4#WIRE#0
U$42: SHORT_A_#_B0
U$43: SHORT_A_#_C0

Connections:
3.3V: C1.1, C7.1, FB1.1, IC1.13, J2.2, J3.2, J4.2, JP0.3, JP1.3, JP10.2, LED0.2, R4.2, R5.2
A0: IC1.1, JP0.2
A1: IC1.2, JP1.2
AIN0: C2.2, C5.2, IC1.11, R7.2
AIN1: C2.1, C3.1, IC1.10, R6.2
AIN2: B0.1, IC1.7
AIN3: A0.2, IC1.6, J1.1, TP1.P$1
GND: C1.2, C3.2, C4.2, C5.1, C7.2, D1.C, IC1.4, IC1.5, J2.1, J3.1, J4.1, JP0.1, JP1.1, R9.1, R10.1
unnamed: A0.1, J1.2, R6.1, TP2.P$1
unnamed: D1.A, R1.1
unnamed: LED0.1, R1.2
unnamed: C4.1, FB1.2, IC1.12
unnamed: B0.2, C0.2, J1.3, R7.1, TP3.P$1
unnamed: C0.1, J1.4, R8.1, R9.2, TP4.P$1
REFN: C6.2, IC1.8, R10.2
REFP: C6.1, IC1.9, R8.2
SCL: IC1.16, J2.4, J3.4, J4.4, R3.1
SCL_PU1: JP10.1, R2.2
SDA: IC1.15, J2.3, J3.3, J4.3, R2.1
SDA_PU1: JP10.3, R3.2
~DRDY: IC1.14, J6.1, R5.1
~RESET: IC1.3, J5.1, R4.1

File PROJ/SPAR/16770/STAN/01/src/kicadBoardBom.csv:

"Id";"Designator";"Package";"Quantity";"Designation";"Supplier and ref";
1;"H2,JP4,JP3,H1";"STAND-OFF";4;"STAND-OFF";;;
2;"C1,C2,C4";"0603";3;"0.1uF";;;
3;"C5,C3";"0603";2;"10nF";;;
4;"LOGO1";"OSHW-LOGO-MINI";1;"OSHW-LOGOMINI";;;
5;"J3";"1X04_NO_SILK";1;"PTH";;;
6;"U$39,U$40";"PWR0";2;"";;;
7;"FB1";"0603";1;"30Ω/1.8A";;;
8;"R9";"0603";1;"1620";;;
9;"R10,R8";"0603";2;"3.9k";;;
10;"R5,R4";"0603";2;"10k";;;
11;"U$21,U$44,U$30";"40";3;"";;;
12;"D1";"LED-0603";1;"RED";;;
13;"U$16,U$17";"#RESET0";2;"";;;
14;"TP2,TP3,TP1,TP4";"TP_15TH";4;"TEST-POINTTP_15TH_THRU";;;
15;"JP6,JP2,FD2,FD1";"FIDUCIAL-1X2";4;"FIDUCIAL1X2";;;
16;"U$14,U$15";"#DRDY0";2;"";;;
17;"R3,R7,R2,R6";"0603";4;"2.2k";;;
18;"U$7,U$25";"GND4";2;"";;;
19;"U$8";"PT1000";1;"";;;
20;"U$9";"SCL6";1;"";;;
21;"U$3,U$26";"3V33";2;"";;;
22;"U$10";"SDA5";1;"";;;
23;"U$27,U$47,U$38,U$34";"31";4;"";;;
24;"C6";"0603";1;"47nF";;;
25;"R1";"0603";1;"1k";;;
26;"FRAME1";"CREATIVE_COMMONS";1;"FRAME-LETTER";;;
27;"U$2,U$1";"SPARKX-SMALL";2;"SPARKX-LOGO3";;;
28;"U$28,U$46,U$37,U$33";"20";4;"";;;
29;"J5,J6";"1X01_NO_SILK";2;"";;;
30;"J1";"LATCHTERMINAL-5MM-4";1;"";;;
31;"J2,J4";"JST04_1MM_RA";2;"QWIIC_RIGHT_ANGLE";;;
32;"C7";"0603";1;"1.0uF";;;
33;"U$35,U$29";"15";2;"";;;
34;"U$32";"QWIIC1";1;"";;;
35;"IC1";"SOP65P640X120-16N";1;"ADS122C04IPWR";;;
36;"A0,B0,C0";"SMT-JUMPER_2_NO_SILK_ROUND";3;"JUMPER-SMT_2_NO_SILK_ROUND";;;
37;"U$19";"B0";1;"";;;
38;"U$31";"2#WIRE#0";1;"";;;
39;"U$36";"3#WIRE#0";1;"";;;
40;"U$13";"_4_0";1;"";;;
41;"U$6";"_2_0";1;"";;;
42;"U$41";"4#WIRE#0";1;"";;;
43;"U$24";"SDA1";1;"";;;
44;"JP10";"SMT-JUMPER_3_2-NC_TRACE_SILK";1;"JUMPER-SMT_3_2-NC_TRACE_SILK";;;
45;"JP0,JP1";"SMT-JUMPER_3_1-NC_TRACE_SILK";2;"JUMPER-SMT_3_1-NC_TRACE_SILK";;;
46;"U$4";"_1_0";1;"";;;
47;"U$11";"A00";1;"";;;
48;"U$20";"I_SUPER2_C-()-03";1;"";;;
49;"U$18";"A0";1;"";;;
50;"LED0";"SMT-JUMPER_2_NC_TRACE_SILK";1;"JUMPER-SMT_2_NC_TRACE_SILK";;;
51;"U$12";"_3_0";1;"";;;
52;"U$23";"SCL0";1;"";;;
53;"U$22";"C0";1;"";;;
54;"U$5";"A11";1;"";;;
55;"U$43";"SHORT_A_#_C0";1;"";;;
56;"U$42";"SHORT_A_#_B0";1;"";;;

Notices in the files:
parts and their libraries:
RELEASED UNDER THE CREATIVE COMMONS ATTRIBUTION SHARE-ALIKE 4.0 LICENSE
HTTPS://CREATIVECOMMONS.ORG/LICENSES/BY-SA/4.0
